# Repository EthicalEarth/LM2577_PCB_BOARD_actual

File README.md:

# LM2577_PCB_BOARD_actual
Step-Up converter (stabilizer), Kicad project.

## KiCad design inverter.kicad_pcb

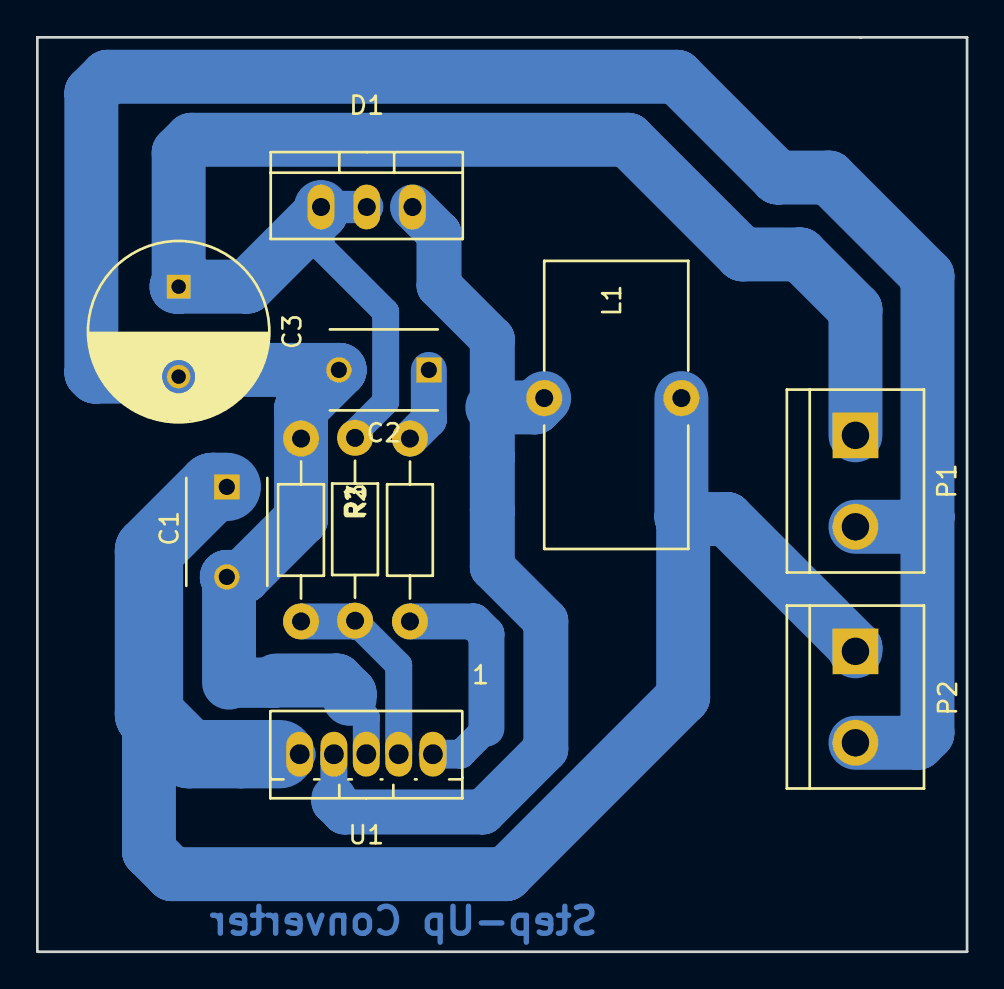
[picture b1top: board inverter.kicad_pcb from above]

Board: 2 copper layers, 51.6 x 50.8 mm, 11 parts (0 on the bottom side), 7 nets.

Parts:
C1, C2: C; C_Disc_D6_P5
C3: CP; C_Radial_D10_L13_P5
D1: D_Schottky_x2_KCom_AKA; TO-220_Neutral123_Vertical
L1: INDUCTOR; Choke_Toroid_8x16mm_Vertical
P1, P2: CONN_01X02; bornier2
R1, R2, R3: R; Resistor_Horizontal_RM10mm
U1: LM1577_LM1577; Pentawatt_Neutral_Straight_Vertical_TO220-5-T05A

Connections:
+5V: C1.1, L1.2, P2.1, U1.5
GND: C1.2, C2.2, C3.2, P1.2, P2.2, R3.2, U1.3
unnamed: C2.1, R1.2
unnamed: C3.1, D1.1, D1.2, P1.1, R2.1
unnamed: D1.3, L1.1, U1.4
unnamed: R1.1, U1.1
unnamed: R2.2, R3.1, U1.2

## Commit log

2018-07-28 Init
